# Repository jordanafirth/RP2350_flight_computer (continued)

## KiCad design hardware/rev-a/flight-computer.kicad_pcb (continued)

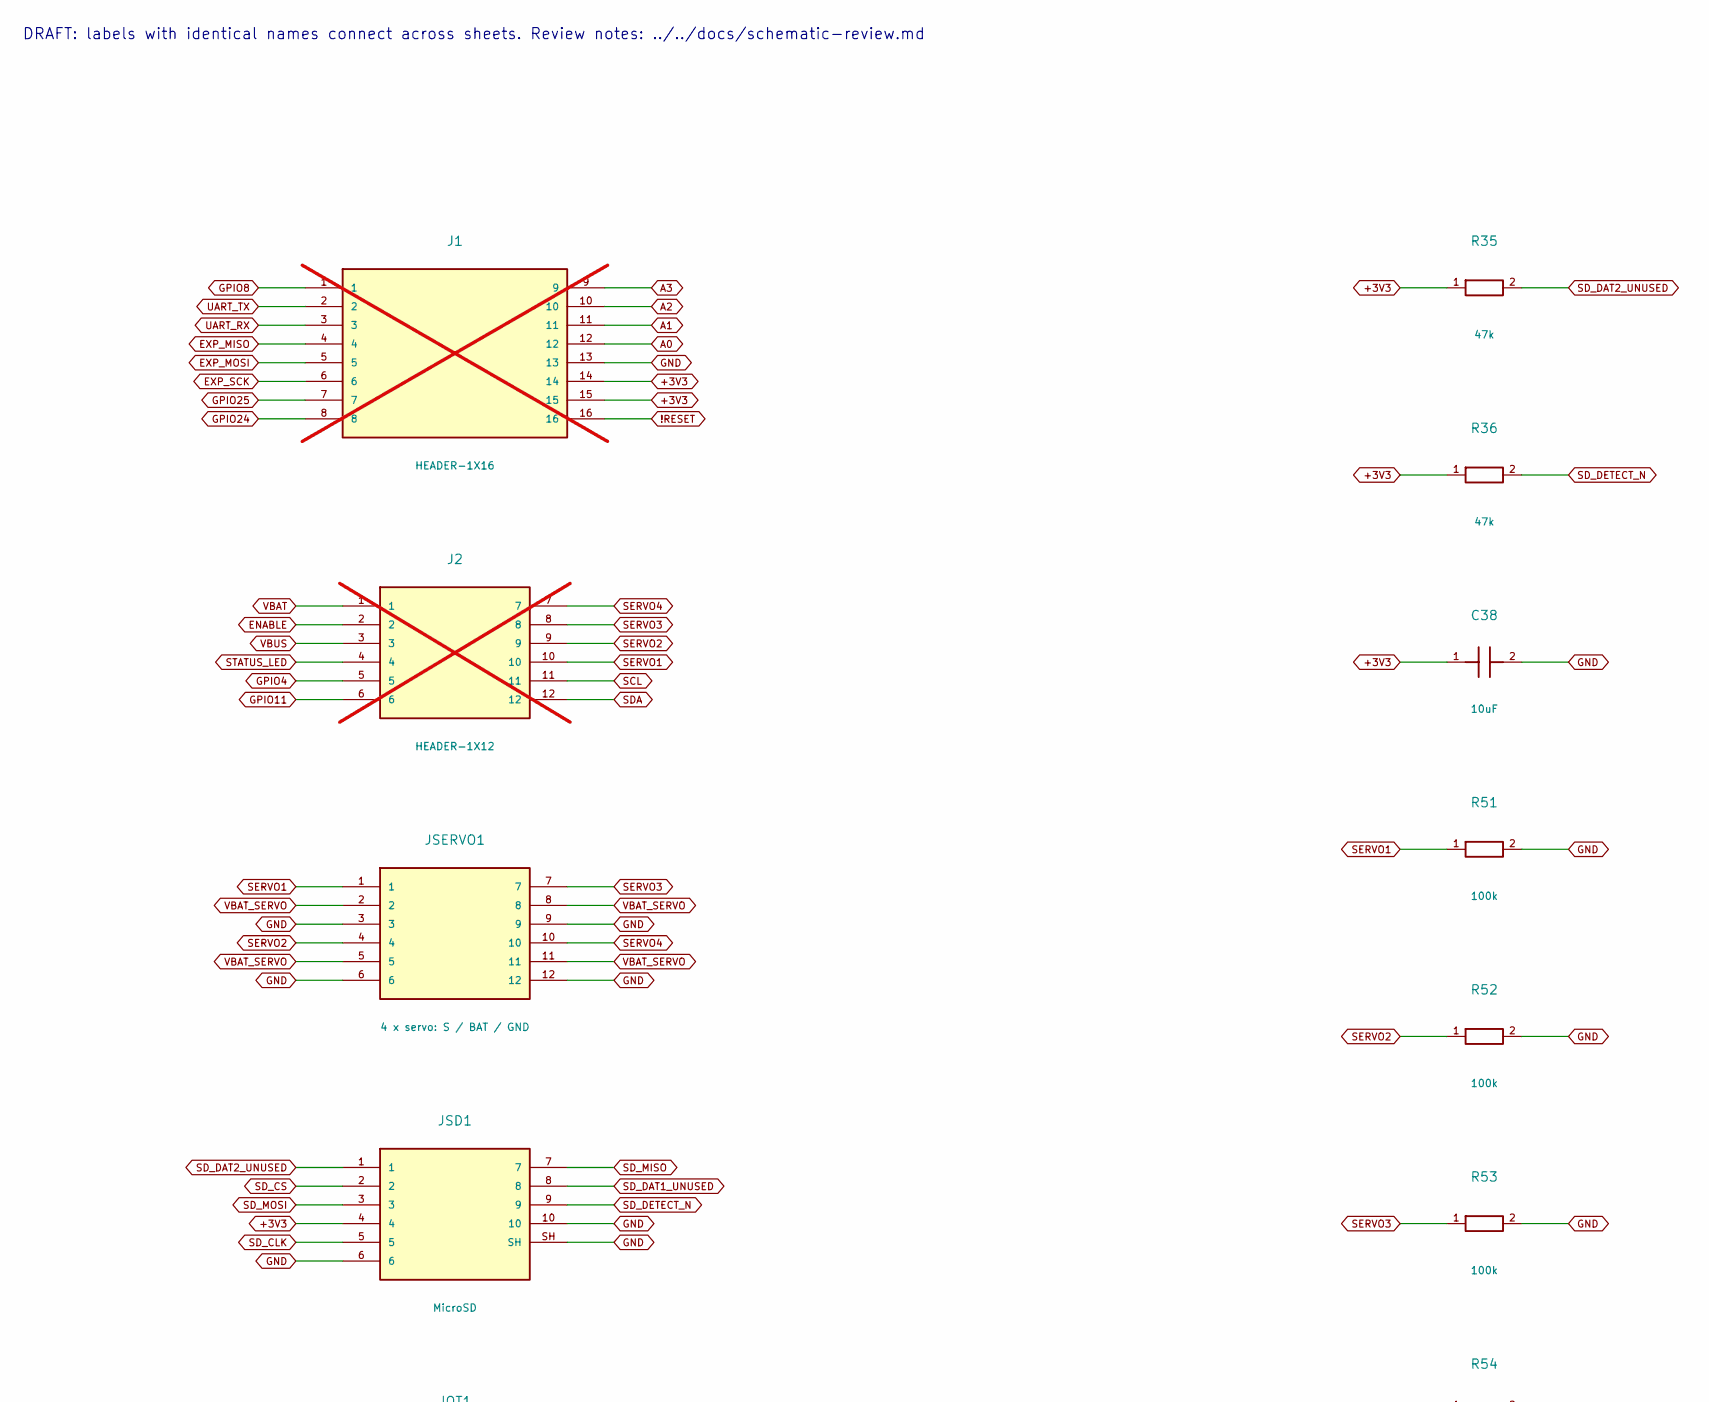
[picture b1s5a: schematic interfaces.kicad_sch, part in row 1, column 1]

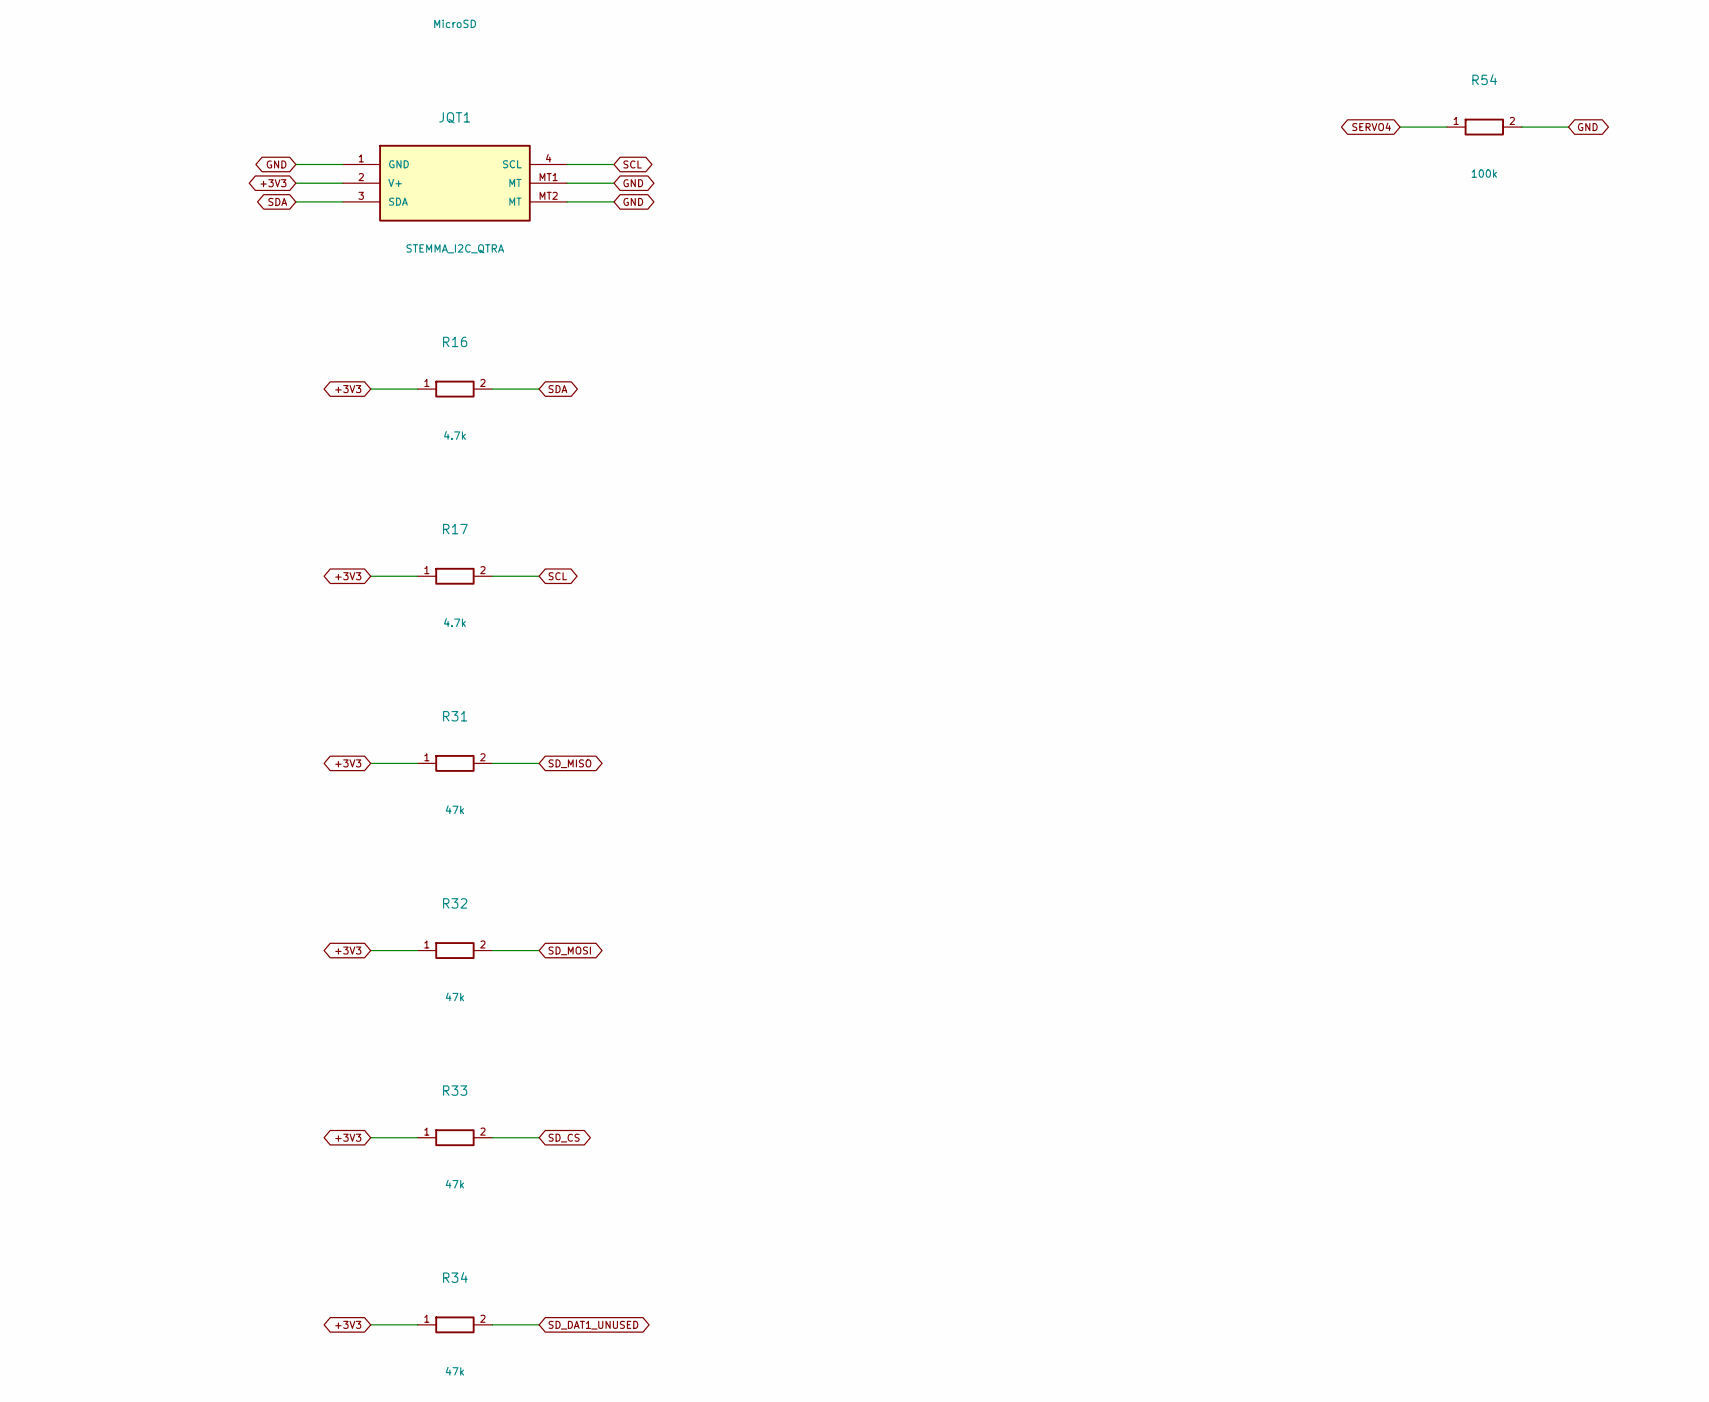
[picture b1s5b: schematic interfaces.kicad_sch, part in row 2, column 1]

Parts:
C38: 10uF; C_0805_2012Metric; MPN GRM21BR61A106KE19L
J1: HEADER-1X16; 1X16_ROUND; not fitted
J2: HEADER-1X12; 1X12_ROUND; not fitted
JQT1: STEMMA_I2C_QTRA; JST_SH4_RA; MPN SM04B-SRSS-TB(LF)(SN)
JSD1: MicroSD; microSD_HC_Molex_104031-0811; MPN 1040310811
JSERVO1: 4 x servo: S / BAT / GND; Servo_RA_3x04_P2.54mm_TSW10408; MPN TSW-104-08-T-T-RA
R16, R17: 4.7k; _0402NO; MPN RC0402FR-074K7L
R31, R32, R33, R34, R35, R36: 47k; R_0603_1608Metric; MPN RC0603FR-0747KL
R51, R52, R53, R54: 100k; R_0603_1608Metric; MPN RC0603FR-07100KL

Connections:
!RESET: J1.16; also elsewhere on the board
+3V3: C38.1, J1.14, J1.15, JQT1.2 (V+), JSD1.4, R16.1, R17.1, R31.1, R32.1, R33.1, R34.1, R35.1, R36.1; also elsewhere on the board
A0: J1.12; also elsewhere on the board
A1: J1.11; also elsewhere on the board
A2: J1.10; also elsewhere on the board
A3: J1.9; also elsewhere on the board
ENABLE: J2.2; also elsewhere on the board
EXP_MISO: J1.4; also elsewhere on the board
EXP_MOSI: J1.5; also elsewhere on the board
EXP_SCK: J1.6; also elsewhere on the board
GND: C38.2, J1.13, JQT1.1 (GND), JQT1.MT1 (MT), JQT1.MT2 (MT), JSD1.6, JSD1.10, JSD1.SH, JSERVO1.3, JSERVO1.6, JSERVO1.9, JSERVO1.12, R51.2, R52.2, R53.2, R54.2; also elsewhere on the board
GPIO4: J2.5; also elsewhere on the board
GPIO8: J1.1; also elsewhere on the board
GPIO11: J2.6; also elsewhere on the board
GPIO24: J1.8; also elsewhere on the board
GPIO25: J1.7; also elsewhere on the board
SCL: J2.11, JQT1.4 (SCL), R17.2; also elsewhere on the board
SDA: J2.12, JQT1.3 (SDA), R16.2; also elsewhere on the board
SD_CLK: JSD1.5; also elsewhere on the board
SD_CS: JSD1.2, R33.2; also elsewhere on the board
SD_DAT1_UNUSED: JSD1.8, R34.2
SD_DAT2_UNUSED: JSD1.1, R35.2
SD_DETECT_N: JSD1.9, R36.2; also elsewhere on the board
SD_MISO: JSD1.7, R31.2; also elsewhere on the board
SD_MOSI: JSD1.3, R32.2; also elsewhere on the board
SERVO1: J2.10, JSERVO1.1, R51.1; also elsewhere on the board
SERVO2: J2.9, JSERVO1.4, R52.1; also elsewhere on the board
SERVO3: J2.8, JSERVO1.7, R53.1; also elsewhere on the board
SERVO4: J2.7, JSERVO1.10, R54.1; also elsewhere on the board
STATUS_LED: J2.4; also elsewhere on the board
UART_RX: J1.3; also elsewhere on the board
UART_TX: J1.2; also elsewhere on the board
VBAT: J2.1; also elsewhere on the board
VBAT_SERVO: JSERVO1.2, JSERVO1.5, JSERVO1.8, JSERVO1.11; also elsewhere on the board
VBUS: J2.3; also elsewhere on the board

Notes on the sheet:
DRAFT: labels with identical names connect across sheets. Review notes: ../../docs/schematic-review.md

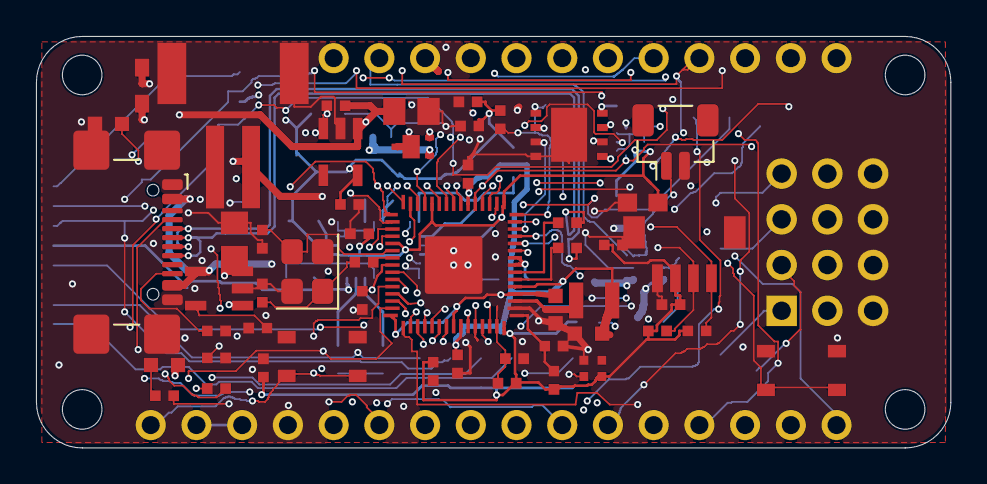
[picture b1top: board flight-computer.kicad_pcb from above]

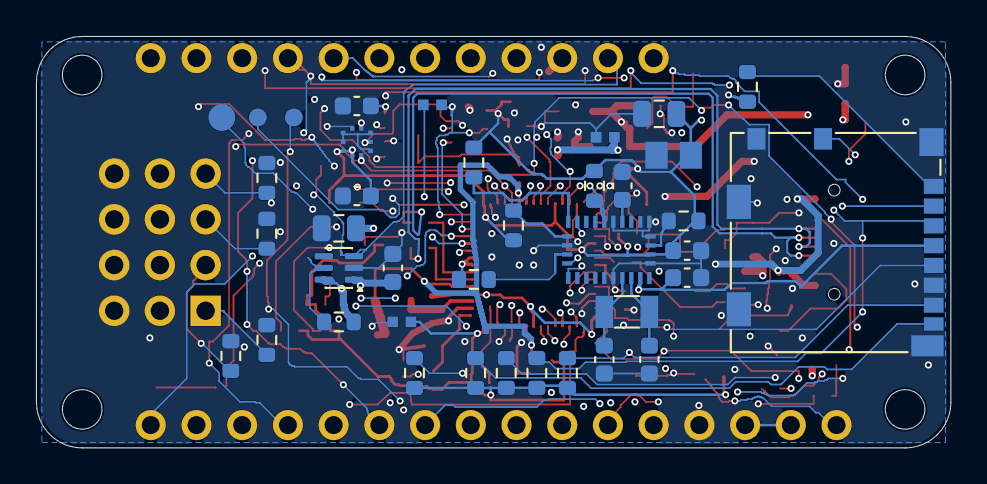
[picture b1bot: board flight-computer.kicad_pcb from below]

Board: 4 copper layers, 50.8 x 22.9 mm, 96 parts (38 on the bottom side), 74 nets.

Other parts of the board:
H1, H2, H3, H4: M2 / max head 3.8mm; MountingHole_M2_Head3.8mm

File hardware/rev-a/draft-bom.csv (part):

Reference,Value,Manufacturer,MPN,Footprint,DNP,Source
C1,10uF,Murata,GRM21BR61A106KE19L,FlightComputer:0805-NO,False,Adafruit-Feather-RP2350-PCB/Adafruit Feather RP2350.sch:C1
C4,10uF,Murata,GRM21BR61A106KE19L,FlightComputer:0805-NO,False,Adafruit-Feather-RP2350-PCB/Adafruit Feather RP2350.sch:C4
D1,RED,Lite-On,LTST-C190KRKT,FlightComputer:CHIPLED_0603_NOOUTLINE,False,Adafruit-Feather-RP2350-PCB/Adafruit Feather RP2350.sch:L
R7,10K,Yageo,RC0402FR-0710KL,FlightComputer:_0402NO,False,Adafruit-Feather-RP2350-PCB/Adafruit Feather RP2350.sch:R7
SW1,KMR2,C&K / Littelfuse,KMR221GLFS,FlightComputer:BTN_RKB2_4.6X2.8,False,Adafruit-Feather-RP2350-PCB/Adafruit Feather RP2350.sch:SW1
U2,RT9080-3.3,Richtek,RT9080-33GJ5,FlightComputer:SOT23-5,False,Adafruit-Feather-RP2350-PCB/Adafruit Feather RP2350.sch:U2
J1,HEADER-1X16,,,FlightComputer:1X16_ROUND,True,Adafruit-Feather-RP2350-PCB/Adafruit Feather RP2350.sch:JP1
JBAT1,JSTPH,JST,S2B-PH-SM4-TB(LF)(SN),FlightComputer:JSTPH2_BATT,False,Adafruit-Feather-RP2350-PCB/Adafruit Feather RP2350.sch:X1
J2,HEADER-1X12,,,FlightComputer:1X12_ROUND,True,Adafruit-Feather-RP2350-PCB/Adafruit Feather RP2350.sch:JP3
U3,MCP73831T-2ACI/OT,Microchip,MCP73831T-2ACI/OT,FlightComputer:SOT23-5,False,Adafruit-Feather-RP2350-PCB/Adafruit Feather RP2350.sch:U3
D2,ORANGE,Lite-On,LTST-C190KFKT,FlightComputer:CHIPLED_0603_NOOUTLINE,False,Adafruit-Feather-RP2350-PCB/Adafruit Feather RP2350.sch:CHG
R2,10K,Yageo,RC0402FR-0710KL,FlightComputer:_0402NO,False,Adafruit-Feather-RP2350-PCB/Adafruit Feather RP2350.sch:R2
C20,10uF,Murata,GRM21BR61A106KE19L,FlightComputer:0805-NO,False,Adafruit-Feather-RP2350-PCB/Adafruit Feather RP2350.sch:C20
R8,5.1k,Yageo,RC0402FR-075K1L,FlightComputer:_0402NO,False,Adafruit-Feather-RP2350-PCB/Adafruit Feather RP2350.sch:R8
C5,10uF,Murata,GRM188R60J106ME47D,FlightComputer:0603-NO,False,Adafruit-Feather-RP2350-PCB/Adafruit Feather RP2350.sch:C5
D5,WS2812B_SK6805_1515,OPSCO,SK6805-EC15,FlightComputer:SK6805_1515,True,Adafruit-Feather-RP2350-PCB/Adafruit Feather RP2350.sch:LED1
U1,8MB QSPI,Winbond,W25Q64JVXGIQ,FlightComputer:USON8_4X4,False,Adafruit-Feather-RP2350-PCB/Adafruit Feather RP2350.sch:U1
R5,10K,Yageo,RC0402FR-0710KL,FlightComputer:_0402NO,False,Adafruit-Feather-RP2350-PCB/Adafruit Feather RP2350.sch:R5
C9,0.1uF,Murata,GRM155R71C104KA88D,FlightComputer:_0402NO,False,Adafruit-Feather-RP2350-PCB/Adafruit Feather RP2350.sch:C9
C10,1uF,Murata,GRM155R61A105KE15D,FlightComputer:_0402NO,False,Adafruit-Feather-RP2350-PCB/Adafruit Feather RP2350.sch:C10
D4,PMEG2020AEA,Nexperia,"PMEG2020AEA,115",FlightComputer:SOD-323F,False,Adafruit-Feather-RP2350-PCB/Adafruit Feather RP2350.sch:D4
Q3,DMP2045UFY4,Diodes Incorporated,DMP2045UFY4-7,FlightComputer:DFN2015-3,False,Adafruit-Feather-RP2350-PCB/Adafruit Feather RP2350.sch:Q3
R3,10K,Yageo,RC0402FR-0710KL,FlightComputer:_0402NO,False,Adafruit-Feather-RP2350-PCB/Adafruit Feather RP2350.sch:R3
JUSB1,USB Type C,GCT,USB4110-GF-A,Connector_USB:USB_C_Receptacle_GCT_USB4110,False,Adafruit-Feather-RP2350-PCB/Adafruit Feather RP2350.sch:X6
R12,5.1K,Yageo,RC0402FR-075K1L,FlightComputer:_0402NO,False,Adafruit-Feather-RP2350-PCB/Adafruit Feather RP2350.sch:R12
R13,5.1K,Yageo,RC0402FR-075K1L,FlightComputer:_0402NO,False,Adafruit-Feather-RP2350-PCB/Adafruit Feather RP2350.sch:R13
Y1,12MHz/10pF/50ohm,Abracon,ABM8-272-T3,Crystal:Crystal_SMD_3225-4Pin_3.2x2.5mm,False,Adafruit-Feather-RP2350-PCB/Adafruit Feather RP2350.sch:Y1
R4,10K,Yageo,RC0402FR-0710KL,FlightComputer:_0402NO,False,Adafruit-Feather-RP2350-PCB/Adafruit Feather RP2350.sch:R4
C6,0.1uF,Murata,GRM155R71C104KA88D,FlightComputer:_0402NO,False,Adafruit-Feather-RP2350-PCB/Adafruit Feather RP2350.sch:C6
C7,0.1uF,Murata,GRM155R71C104KA88D,FlightComputer:_0402NO,False,Adafruit-Feather-RP2350-PCB/Adafruit Feather RP2350.sch:C7
C8,10uF_0603,Murata,GRM188R60J106ME47D,FlightComputer:_0603MP,False,Adafruit-Feather-RP2350-PCB/Adafruit Feather RP2350.sch:C8
C11,1uF,Murata,GRM155R61A105KE15D,FlightComputer:_0402NO,False,Adafruit-Feather-RP2350-PCB/Adafruit Feather RP2350.sch:C11
C12,0.1uF,Murata,GRM155R71C104KA88D,FlightComputer:_0402NO,False,Adafruit-Feather-RP2350-PCB/Adafruit Feather RP2350.sch:C12
C13,10uF_0603,Murata,GRM188R60J106ME47D,FlightComputer:_0603MP,False,Adafruit-Feather-RP2350-PCB/Adafruit Feather RP2350.sch:C13
C14,0.1uF,Murata,GRM155R71C104KA88D,FlightComputer:_0402NO,False,Adafruit-Feather-RP2350-PCB/Adafruit Feather RP2350.sch:C14
C15,1uF,Murata,GRM155R61A105KE15D,FlightComputer:_0402NO,False,Adafruit-Feather-RP2350-PCB/Adafruit Feather RP2350.sch:C15
C16,0.1uF,Murata,GRM155R71C104KA88D,FlightComputer:_0402NO,False,Adafruit-Feather-RP2350-PCB/Adafruit Feather RP2350.sch:C16
C2,15pF,Murata,GRM1555C1H150JA01D,FlightComputer:_0402NO,False,Adafruit-Feather-RP2350-PCB/Adafruit Feather RP2350.sch:C2
C3,15pF,Murata,GRM1555C1H150JA01D,FlightComputer:_0402NO,False,Adafruit-Feather-RP2350-PCB/Adafruit Feather RP2350.sch:C3
R6,1K,Yageo,RC0402FR-071KL,FlightComputer:_0402NO,False,Adafruit-Feather-RP2350-PCB/Adafruit Feather RP2350.sch:R6
R9,27 ohm,Yageo,RC0402FR-0727RL,FlightComputer:_0402NO,False,Adafruit-Feather-RP2350-PCB/Adafruit Feather RP2350.sch:R9
R10,27 ohm,Yageo,RC0402FR-0727RL,FlightComputer:_0402NO,False,Adafruit-Feather-RP2350-PCB/Adafruit Feather RP2350.sch:R10
SW2,KMR2,C&K / Littelfuse,KMR221GLFS,FlightComputer:BTN_RKB2_4.6X2.8,False,Adafruit-Feather-RP2350-PCB/Adafruit Feather RP2350.sch:SW2
R11,1K,Yageo,RC0402FR-071KL,FlightComputer:_0402NO,False,Adafruit-Feather-RP2350-PCB/Adafruit Feather RP2350.sch:R11
C17,1uF,Murata,GRM155R61A105KE15D,FlightComputer:_0402NO,False,Adafruit-Feather-RP2350-PCB/Adafruit Feather RP2350.sch:C17
C18,0.1uF,Murata,GRM155R71C104KA88D,FlightComputer:_0402NO,False,Adafruit-Feather-RP2350-PCB/Adafruit Feather RP2350.sch:C18
U4,RP2350A (A4),Raspberry Pi,SC1509-A4,FlightComputer:QFN60_7MM_REDUCEDEPAD,False,Adafruit-Feather-RP2350-PCB/Adafruit Feather RP2350.sch:X2
R21,10K,Yageo,RC0402FR-0710KL,FlightComputer:_0402NO,False,Adafruit-Feather-RP2350-PCB/Adafruit Feather RP2350.sch:R21
R1,200,Yageo,RC0402FR-07200RL,FlightComputer:_0402NO,False,Adafruit-Feather-RP2350-PCB/Adafruit Feather RP2350.sch:R1
C19,2.2uF,Murata,GRM155R61A225KE01D,FlightComputer:_0402NO,False,Adafruit-Feather-RP2350-PCB/Adafruit Feather RP2350.sch:C19
R14,10,Yageo,RC0402FR-0710RL,FlightComputer:_0402NO,False,Adafruit-Feather-RP2350-PCB/Adafruit Feather RP2350.sch:R14
C21,2.2uF,Murata,GRM155R61A225KE01D,FlightComputer:_0402NO,False,Adafruit-Feather-RP2350-PCB/Adafruit Feather RP2350.sch:C21
L1,DFE252012F-3R3M=P2,TDK,DFE252012F-3R3M=P2,FlightComputer:INDUCTOR_1007,False,Adafruit-Feather-RP2350-PCB/Adafruit Feather RP2350.sch:L1
R16,4.7k,Yageo,RC0402FR-074K7L,FlightComputer:_0402NO,False,Adafruit-Feather-RP2350-PCB/Adafruit Feather RP2350.sch:R16
R17,4.7k,Yageo,RC0402FR-074K7L,FlightComputer:_0402NO,False,Adafruit-Feather-RP2350-PCB/Adafruit Feather RP2350.sch:R17
JQT1,STEMMA_I2C_QTRA,JST,SM04B-SRSS-TB(LF)(SN),FlightComputer:JST_SH4_RA,False,Adafruit-Feather-RP2350-PCB/Adafruit Feather RP2350.sch:CONN1
U5,BNO085,CEVA,BNO085,FlightComputer:BNO080,False,Adafruit-BNO08x-PCB/Adafruit_BNO08x.sch:U1
Y2,32.768kHz,Abracon,ABS07-32.768KHZ-T,Crystal:Crystal_SMD_3215-2Pin_3.2x1.5mm,False,Adafruit-BNO08x-PCB/Adafruit_BNO08x.sch:X1
C31,100nF,Murata,GRM188R71H104KA93D,Capacitor_SMD:C_0603_1608Metric,False,Custom integration
C32,100nF,Murata,GRM188R71H104KA93D,Capacitor_SMD:C_0603_1608Metric,False,Custom integration
C33,22pF,Murata,GRM1885C1H220JA01D,Capacitor_SMD:C_0603_1608Metric,False,Custom integration
C34,22pF,Murata,GRM1885C1H220JA01D,Capacitor_SMD:C_0603_1608Metric,False,Custom integration
C35,100nF,Murata,GRM188R71H104KA93D,Capacitor_SMD:C_0603_1608Metric,False,Custom integration
R41,10k,Yageo,RC0603FR-0710KL,Resistor_SMD:R_0603_1608Metric,False,Custom integration
R42,10k,Yageo,RC0603FR-0710KL,Resistor_SMD:R_0603_1608Metric,False,Custom integration
R43,10k,Yageo,RC0603FR-0710KL,Resistor_SMD:R_0603_1608Metric,False,Custom integration
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
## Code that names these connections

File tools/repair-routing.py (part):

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routes=[];failed=[];began=time.time()
connections=drc['unconnected_items']
if args.inner_crossings:
    priority={'SD_MOSI':0,'QSPI_IO3':1,'SWDIO':2,'BMP_INT':3,'A0':4,'GPIO8':5,'SERVO2':6}
    connections=sorted(connections,key=lambda c:min((rank for net,rank in priority.items() if '['+net+']' in c['items'][0]['description']),default=50))
if args.ground_fanout:
    args.fanout=True
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
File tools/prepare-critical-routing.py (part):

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    v.SetNet(b.FindNet(net)); v.SetLocked(True); b.Add(v)

if args.escape_flash:
    wire('BNO_AUX_SDA',[loc('U5','16'),(125.5,111.11)],pcbnew.B_Cu,.15)
    via('BNO_AUX_SDA',(125.5,111.11));via('BNO_AUX_SDA',(126.5,108.8))
    wire('BNO_AUX_SDA',[(125.5,111.11),(126.5,110.11),(126.5,108.8)],pcbnew.In2_Cu,.15)
    wire('BNO_AUX_SDA',[(126.5,108.8),(126.5,106),loc('R45','2')],pcbnew.B_Cu,.15)
    wire('BNO_CS_N',[loc('U5','18'),(126.98,112.11),(126.98,114.305),loc('R43','2')],pcbnew.B_Cu,.15)
else:
    wire('BNO_AUX_SDA', [loc('U5','16'), (126.98,111.11), (127.69,110.4),
         (128.65,110.4), (128.65,107.225), loc('R45','2')], pcbnew.B_Cu, .15)
# Connector's duplicate contacts need explicit jumps; an ordinary pair route
# cannot connect the interleaved D-/D+/D-/D+ land ordering without a crossing.
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wire('GND',[(128.1,115.8),(127.9,115.8)],width=.2)
wire('GND',[loc('C8','2'),(129.9085,117.4)],width=.35)
for xy in [(127.9,115.8),(129.9085,117.4)]:via('GND',xy)
wire('VCORE',[loc('L1','P$1'),loc('C8','1')],width=.5)
feedback=([loc('U4','50'),(127.7,113.9),(127.835,113.765),(129.1,113.765),(129.965,112.9),(131.988,112.9),loc('L1','P$1')]
          if args.escape_flash else [loc('U4','50'),(128,113.9),(129,112.9),(131.988,112.9),loc('L1','P$1')])
wire('VCORE',feedback,width=.15)
wire('VREG_AVDD',[loc('U4','46'),(127.3,115.5),(127.3,116.258),loc('C21','1')],width=.15)
wire('VREG_AVDD',[loc('C21','1'),(128.242,118.084),loc('R14','2')],width=.15)
wire('GND',[loc('C21','2'),(129.9085,117.4)],width=.2)

output=(132.3,116.65);top=(124.025,108.7) if args.escape_flash else (122.4,108.158)
left=(118.075,113.3);bottom=(123.25,116.85)
for xy in [output,top,left,bottom]:via('VCORE',xy)
wire('VCORE',[loc('C8','1'),output],width=.4)
wire('VCORE',[loc('U4','6'),loc('C7','2')],width=.15)
wire('VCORE',[loc('C7','2'),top],width=.2)
wire('VCORE',[loc('U4','23'),(119.1925,112.7),(119.1925,113.05),(118.9425,113.3),left,loc('C18','2')],width=.13)
wire('VCORE',[loc('U4','39'),(123.5775,116.7),(123.4275,116.85),bottom,loc('C6','2')],width=.15)
trunk_x=128.9 if args.escape_flash else 128.4
if args.escape_flash:
    wire('VCORE',[output,(130.6,114.95),(trunk_x,114.95),(trunk_x,106.4),(124.025,106.4),top],pcbnew.In2_Cu,.3)
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
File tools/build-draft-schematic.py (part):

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    crystal = add(imu['X1'], 'Y2', 'Sensors')
    crystal['value'] = '32.768kHz'
    for pin in crystal['pins']:
        pin['net'] = {'XIN': 'BNO_XIN', 'XOUT': 'BNO_XOUT'}.get(pin['net'], pin['net'])
    cap = 'Capacitor_SMD:C_0603_1608Metric'
    resistor = 'Resistor_SMD:R_0603_1608Metric'
    for ref, value, net in [('C31', '100nF', 'BNO_CAP'), ('C32', '100nF', '+3V3'), ('C33', '22pF', 'BNO_XIN'), ('C34', '22pF', 'BNO_XOUT'), ('C35', '100nF', '+3V3')]:
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        simple(f'R{index}', '47k', ['+3V3', net], 'Interfaces', resistor)
    simple('C38', '10uF', ['+3V3', 'GND'], 'Interfaces', 'Capacitor_SMD:C_0805_2012Metric')
    simple('JTAG1', 'REMOVE BEFORE FLIGHT', ['ENABLE', 'GND'], 'Power', 'Connector_JST:JST_SH_BM02B-SRSS-TB_1x02-1MP_P1.00mm_Vertical', 'BM02B-SRSS-TB(LF)(SN)')
    servo_pins = [net for i in range(1, 5) for net in (f'SERVO{i}', 'VBAT_SERVO', 'GND')]
    simple('JSERVO1', '4 x servo: S / BAT / GND', servo_pins, 'Interfaces', 'FlightComputer:Servo_RA_3x04_P2.54mm_TSW10408', 'TSW-104-08-T-T-RA')
    for i in range(1, 5):
        simple(f'R{50+i}', '100k', [f'SERVO{i}', 'GND'], 'Interfaces', resistor)
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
